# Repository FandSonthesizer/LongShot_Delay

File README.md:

# LongShot_Delay
This is the evolution of our wire-head delay pedal. Here we add a wobble effect top simulate a worn tape drive, where the motors and belts are quite old.

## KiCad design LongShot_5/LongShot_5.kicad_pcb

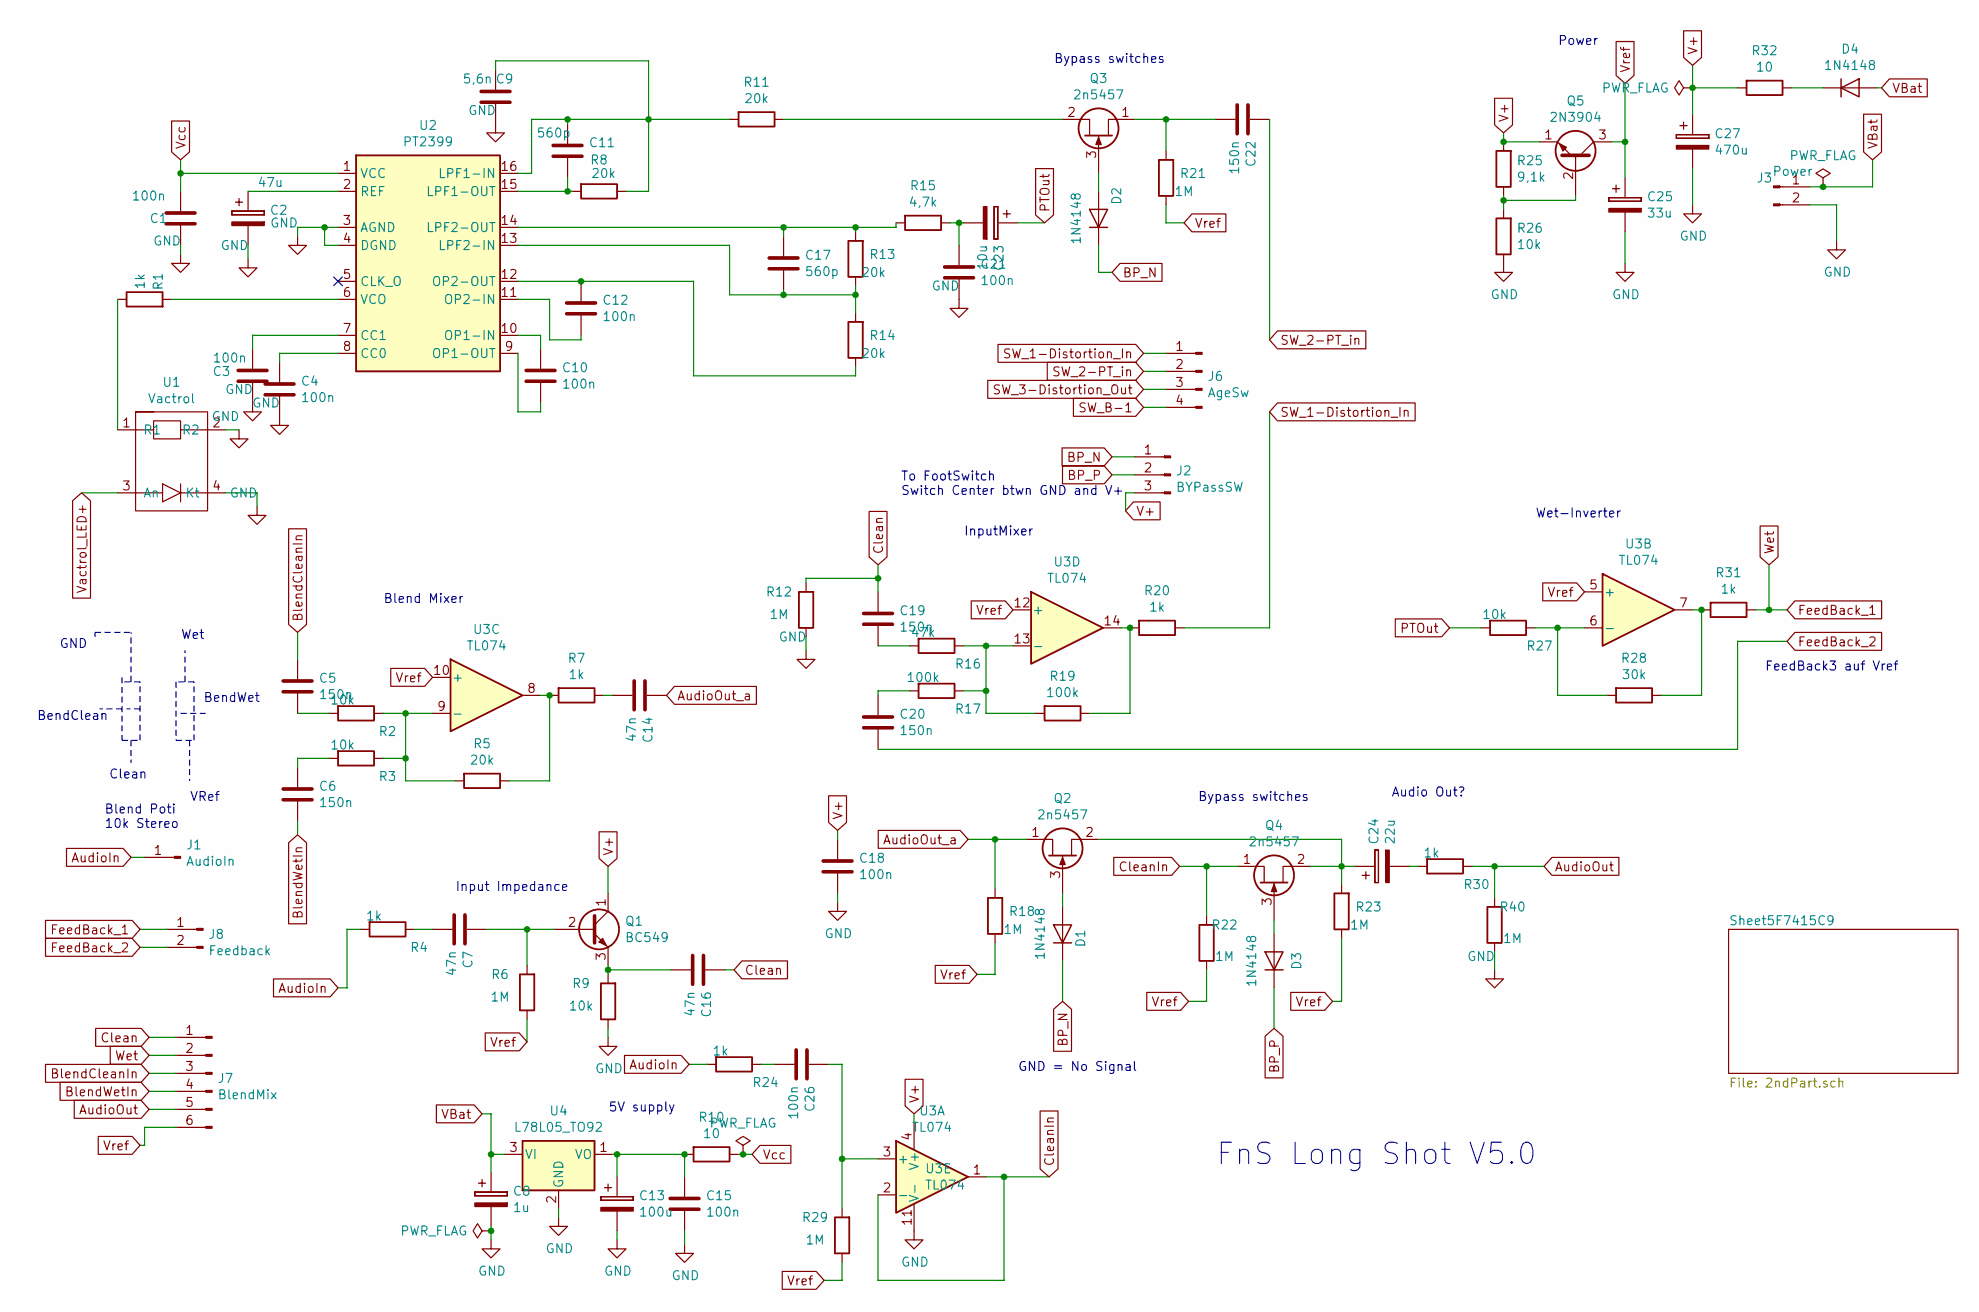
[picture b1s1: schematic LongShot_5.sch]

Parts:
C1, C3, C4, C10, C12, C15, C18, C21, C26: 100n; Kondensator_Keramik
C2: 47u; Elko_D6.3mm_P2.50mm
C5, C6, C19, C20, C22: 150n; Kondensator_Keramik
C7, C14, C16: 47n; Kondensator_Keramik
C8: 1u; Elko_D6.3mm_P2.50mm
C9: 5,6n; Kondensator_Keramik
C11, C17: 560p; Kondensator_Keramik
C13: 100u; Elko_D6.3mm_P2.50mm
C23: 10u; Elko_D6.3mm_P2.50mm
C24: 22u; Elko_D6.3mm_P2.50mm
C25: 33u; Elko_D6.3mm_P2.50mm
C27: 470u; Elko_D6.3mm_P2.50mm
D1, D2, D3, D4: 1N4148; Diode_Horizontal
J1: AudioIn; Stift
J2: BYPassSW; Stift_0x3
J3: Power; Stift_x02
J6: AgeSw; PinHeader_1x04_P2.54mm_Vertical_NIK
J7: BlendMix; PinHeader_1x06_P2.54mm_Vertical_NIK
J8: Feedback; Stift_x02
Q1: BC549; TO-92_Wide_NIK
Q2, Q3, Q4: 2n5457; TO-92_Wide_NIK
Q5: 2N3904; TO-92_Wide_NIK
R1, R4, R7, R20, R24, R30, R31: 1k; Widerstand_liegend
R2, R3, R9, R26, R27: 10k; Widerstand_liegend
R5, R8, R11, R13, R14: 20k; Widerstand_liegend
R6, R12, R18, R21, R22, R23, R29, R40: 1M; Widerstand_liegend
R10, R32: 10; Widerstand_liegend
R15: 4,7k; Widerstand_liegend
R16: 47k; Widerstand_liegend
R17, R19: 100k; Widerstand_liegend
R25: 9,1k; Widerstand_liegend
R28: 30k; Widerstand_liegend
U1: Vactrol
U2: PT2399; DIP-16_W7.62mm_Socket_LongPads
U3: TL074; DIP-14_W7.62mm_Socket_LongPads
U4: L78L05_TO92; TO-92_Wide_NIK

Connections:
AudioIn: J1.1, R4.2, R24.2
AudioOut: J7.5, R30.1, R40.2
AudioOut_a: C14.1, Q2.1 (D), R18.2
BP_N: D1.1 (K), D2.1 (K), J2.1
BP_P: D3.1 (K), J2.2
BlendCleanIn: C5.1, J7.3
BlendWetIn: C6.2, J7.4
Clean: C16.1, C19.1, J7.1, R12.2
CleanIn: Q4.1 (D), R22.2, U3.1, U3.2 (-)
DistB_2: J6.3; also elsewhere on the board
FeedBack_1: J7.2, J8.1, R31.1
FeedBack_2: C20.2, J8.2
GND: C1.2, C2.2, C3.1, C4.1, C8.2, C9.1, C13.2, C15.2, C18.2, C21.2, C25.2, C27.2, J3.2, R9.1, R12.1, R26.1, R40.1, U1.2 (R2), U1.4 (Kt), U2.3 (AGND), U2.4 (DGND), U3.11 (V-), U4.2 (GND); also elsewhere on the board
unnamed: C2.1, U2.2 (REF)
unnamed: C3.2, U2.7 (CC1)
unnamed: C4.2, U2.8 (CC0)
unnamed: C5.2, R2.2
unnamed: C6.1, R3.2
unnamed: C7.1, Q1.2 (B), R6.2
unnamed: C7.2, R4.1
unnamed: C10.1, U2.9 (OP1-OUT)
unnamed: C10.2, U2.10 (OP1-IN)
unnamed: C11.1, R8.2, U2.15 (LPF1-OUT)
unnamed: C9.2, C11.2, R8.1, R11.2, U2.16 (LPF1-IN)
unnamed: C12.1, U2.11 (OP2-IN)
unnamed: C12.2, R14.1, U2.12 (OP2-OUT)
unnamed: C13.1, C15.1, R10.2, U4.1 (VO)
unnamed: C14.2, R7.1
unnamed: C16.2, Q1.3 (E), R9.2
unnamed: C17.1, R13.2, R15.2, U2.14 (LPF2-OUT)
unnamed: C17.2, R13.1, R14.2, U2.13 (LPF2-IN)
unnamed: C19.2, R16.2
unnamed: C20.1, R17.2
unnamed: C21.1, C23.2, R15.1
unnamed: C22.2, Q3.1 (D), R21.2
unnamed: C24.1, Q2.2 (S), Q4.2 (S), R23.2
unnamed: C24.2, R30.2
unnamed: C26.1, R29.2, U3.3 (+)
unnamed: C26.2, R24.1
unnamed: D1.2 (A), Q2.3 (G)
unnamed: D2.2 (A), Q3.3 (G)
unnamed: D3.2 (A), Q4.3 (G)
unnamed: D4.1 (K), R32.1
unnamed: Q3.2 (S), R11.1
unnamed: Q5.2 (B), R25.1, R26.2
unnamed: R1.1, U1.1 (R1)
unnamed: R1.2, U2.6 (VCO)
unnamed: R2.1, R3.1, R5.2, U3.9 (-)
unnamed: R5.1, R7.2, U3.8
unnamed: R16.1, R17.1, R19.2, U3.13 (-)
unnamed: R19.1, R20.2, U3.14
unnamed: R27.1, R28.2, U3.6 (-)
unnamed: R28.1, R31.2, U3.7
PTOut: C23.1, R27.2
SW_1-Distortion_In: J6.1, R20.1; also elsewhere on the board
SW_2-PT_in: C22.1, J6.2
SW_B-1: J6.4; also elsewhere on the board
V+: C18.1, C27.1, J2.3, Q1.1 (C), Q5.1 (E), R25.2, R32.2, U3.4 (V+); also elsewhere on the board
VBat: C8.1, D4.2 (A), J3.1, U4.3 (VI)
Vactrol_LED+: U1.3 (An); also elsewhere on the board
Vcc: C1.1, R10.1, U2.1 (VCC)
Vref: C25.1, J7.6, Q5.3 (C), R6.1, R18.1, R21.1, R22.1, R23.1, R29.1, U3.5 (+), U3.10 (+), U3.12 (+); also elsewhere on the board

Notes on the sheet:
FnS Long Shot V5.0
Wet
Clean
BendClean
BendWet
Blend Poti 10k Stereo
Blend Mixer
Power
5V supply
VRef
GND
InputMixer
Wet-Inverter
Input Impedance
FeedBack3 auf Vref
Bypass switches
GND = No Signal
To FootSwitch Switch Center btwn GND and V+
Audio Out?

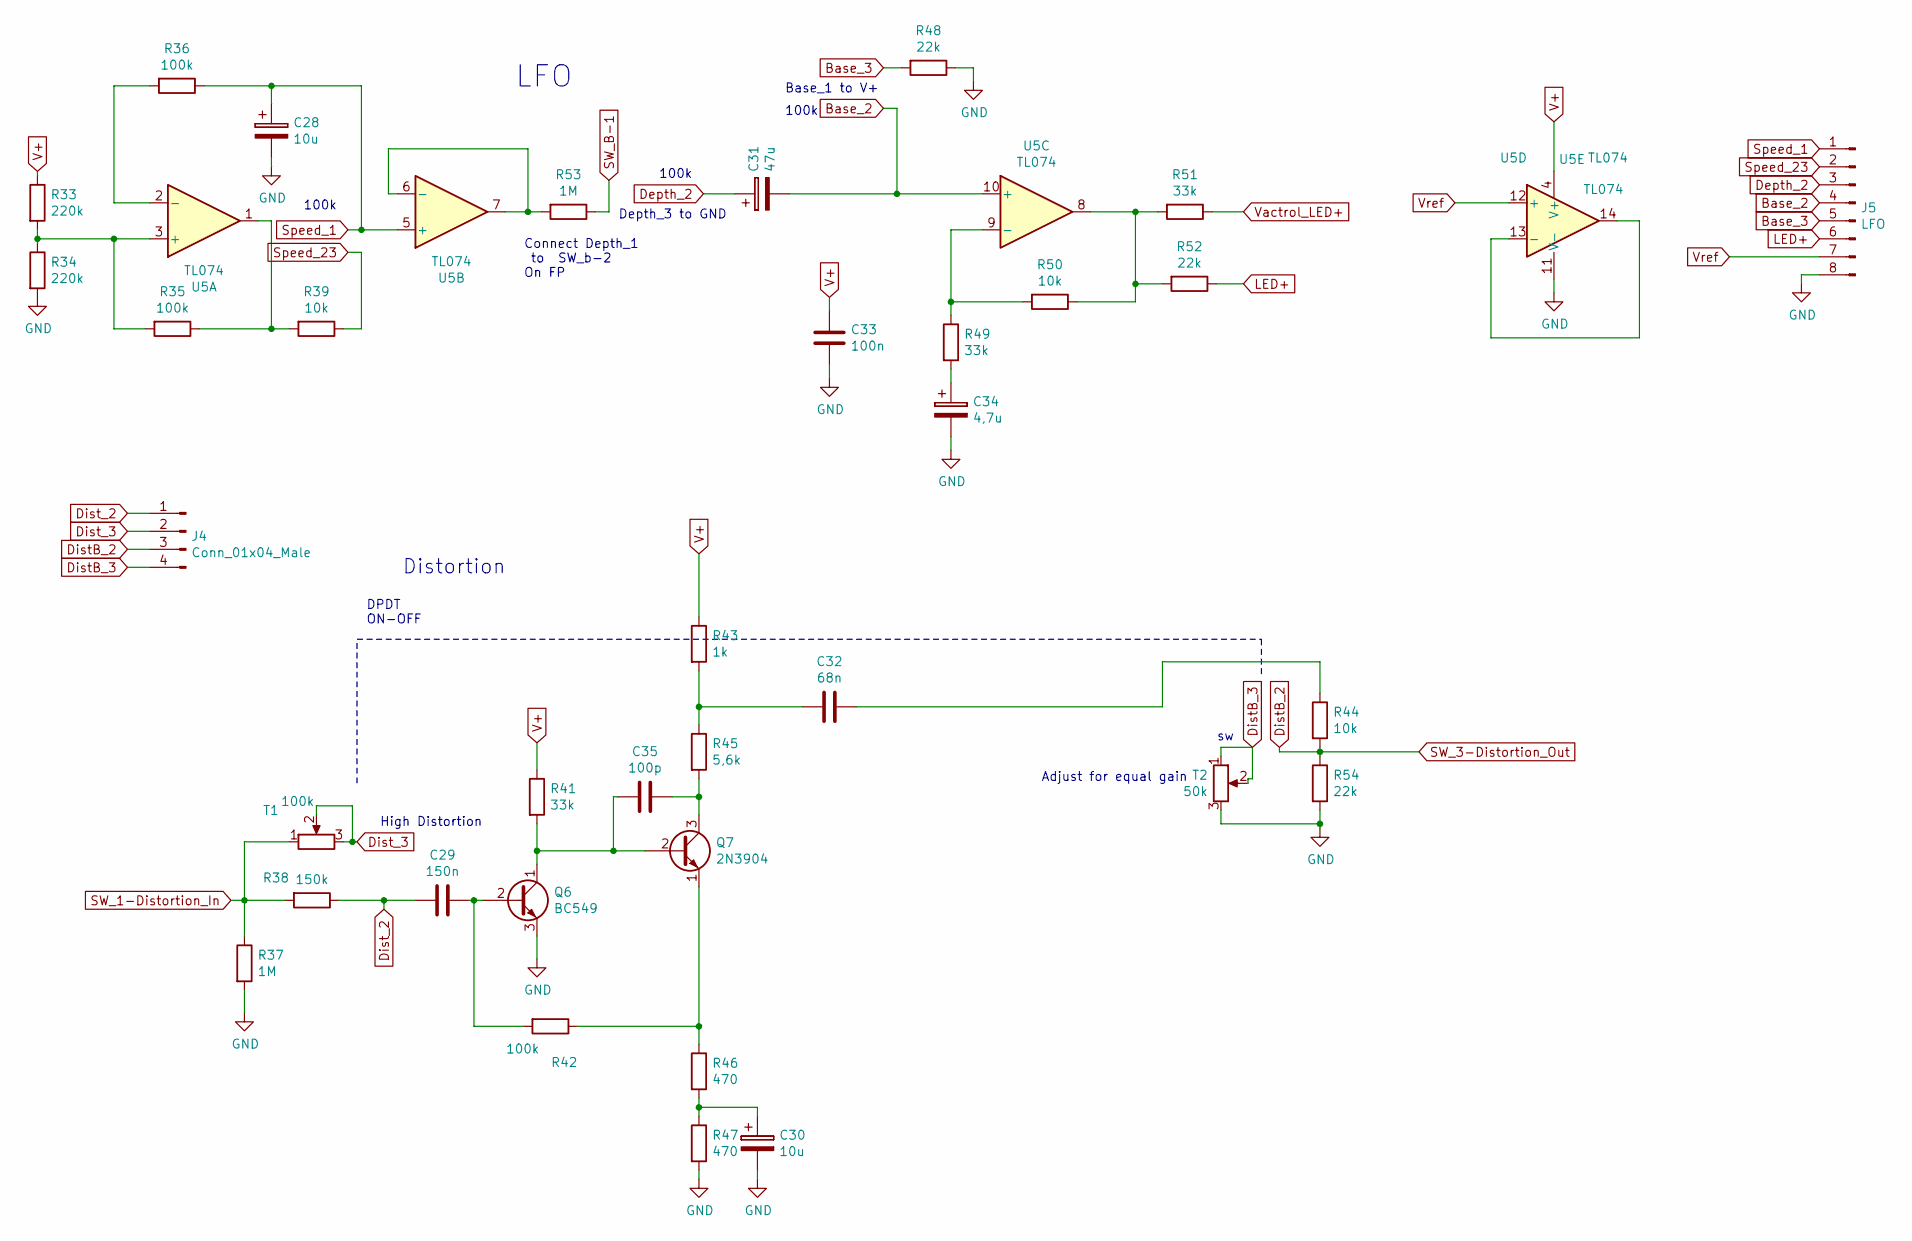
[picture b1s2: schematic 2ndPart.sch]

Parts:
C28, C30: 10u; Elko_D6.3mm_P2.50mm
C29: 150n; Kondensator_Keramik
C31: 47u; Elko_D6.3mm_P2.50mm
C32: 68n; Kondensator_Keramik
C33: 100n; Kondensator_Keramik
C34: 4,7u; Elko_D6.3mm_P2.50mm
C35: 100p; Kondensator_Keramik
J4: Conn_01x04_Male; PinHeader_1x04_P2.54mm_Vertical_NIK
J5: LFO; PinHeader_1x08_P2.54mm_Vertical_Nik
Q6: BC549; TO-92_Wide_NIK
Q7: 2N3904; TO-92_Wide_NIK
R33, R34: 220k; Widerstand_liegend
R35, R36, R42: 100k; Widerstand_liegend
R37, R53: 1M; Widerstand_liegend
R38: 150k; Widerstand_liegend
R39, R44, R50: 10k; Widerstand_liegend
R41, R49, R51: 33k; Widerstand_liegend
R43: 1k; Widerstand_liegend
R45: 5,6k; Widerstand_liegend
R46, R47: 470; Widerstand_liegend
R48, R52, R54: 22k; Widerstand_liegend
T1: 100k; Trimmer_Vertical
T2: 50k; Trimmer_Vertical
U5: TL074; DIP-14_W7.62mm_Socket_LongPads

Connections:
Base_2: C31.2, J5.4, U5.10 (+)
Base_3: J5.5, R48.2
Depth_2: C31.1, J5.3
DistB_2: J4.3, R44.2, R54.1; also elsewhere on the board
DistB_3: J4.4, T2.1, T2.2
Dist_2: C29.2, J4.1, R38.1
Dist_3: J4.2, T1.2, T1.3
GND: C28.2, C30.2, C33.1, C34.2, J5.8, Q6.3 (E), R34.2, R37.2, R47.2, R48.1, R54.2, T2.3, U5.11 (V-); also elsewhere on the board
LED+: J5.6, R52.1
unnamed: C29.1, Q6.2 (B), R42.2
unnamed: C30.1, R46.2, R47.1
unnamed: C32.1, R44.1
unnamed: C32.2, R43.2, R45.1
unnamed: C34.1, R49.2
unnamed: C35.1, Q7.3 (C), R45.2
unnamed: C35.2, Q6.1 (C), Q7.2 (B), R41.2
unnamed: Q7.1 (E), R42.1, R46.1
unnamed: R33.2, R34.1, R35.2, U5.3 (+)
unnamed: R35.1, R39.2, U5.1
unnamed: R36.2, U5.2 (-)
unnamed: R49.1, R50.2, U5.9 (-)
unnamed: R50.1, R51.2, R52.2, U5.8
unnamed: R53.2, U5.6 (-), U5.7
unnamed: U5.13 (-), U5.14
SW_1-Distortion_In: R37.1, R38.2, T1.1; also elsewhere on the board
SW_B-1: R53.1; also elsewhere on the board
Speed_1: C28.1, J5.1, R36.1, U5.5 (+)
Speed_23: J5.2, R39.1
V+: C33.2, R33.1, R41.1, R43.1, U5.4 (V+); also elsewhere on the board
Vactrol_LED+: R51.1; also elsewhere on the board
Vref: J5.7, U5.12 (+); also elsewhere on the board

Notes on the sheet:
DPDT ON-OFF
Distortion
100k
High Distortion
Base_1 to V+
Depth_3 to GND
Connect Depth_1 to SW_b-2 On FP
LFO
Adjust for equal gain

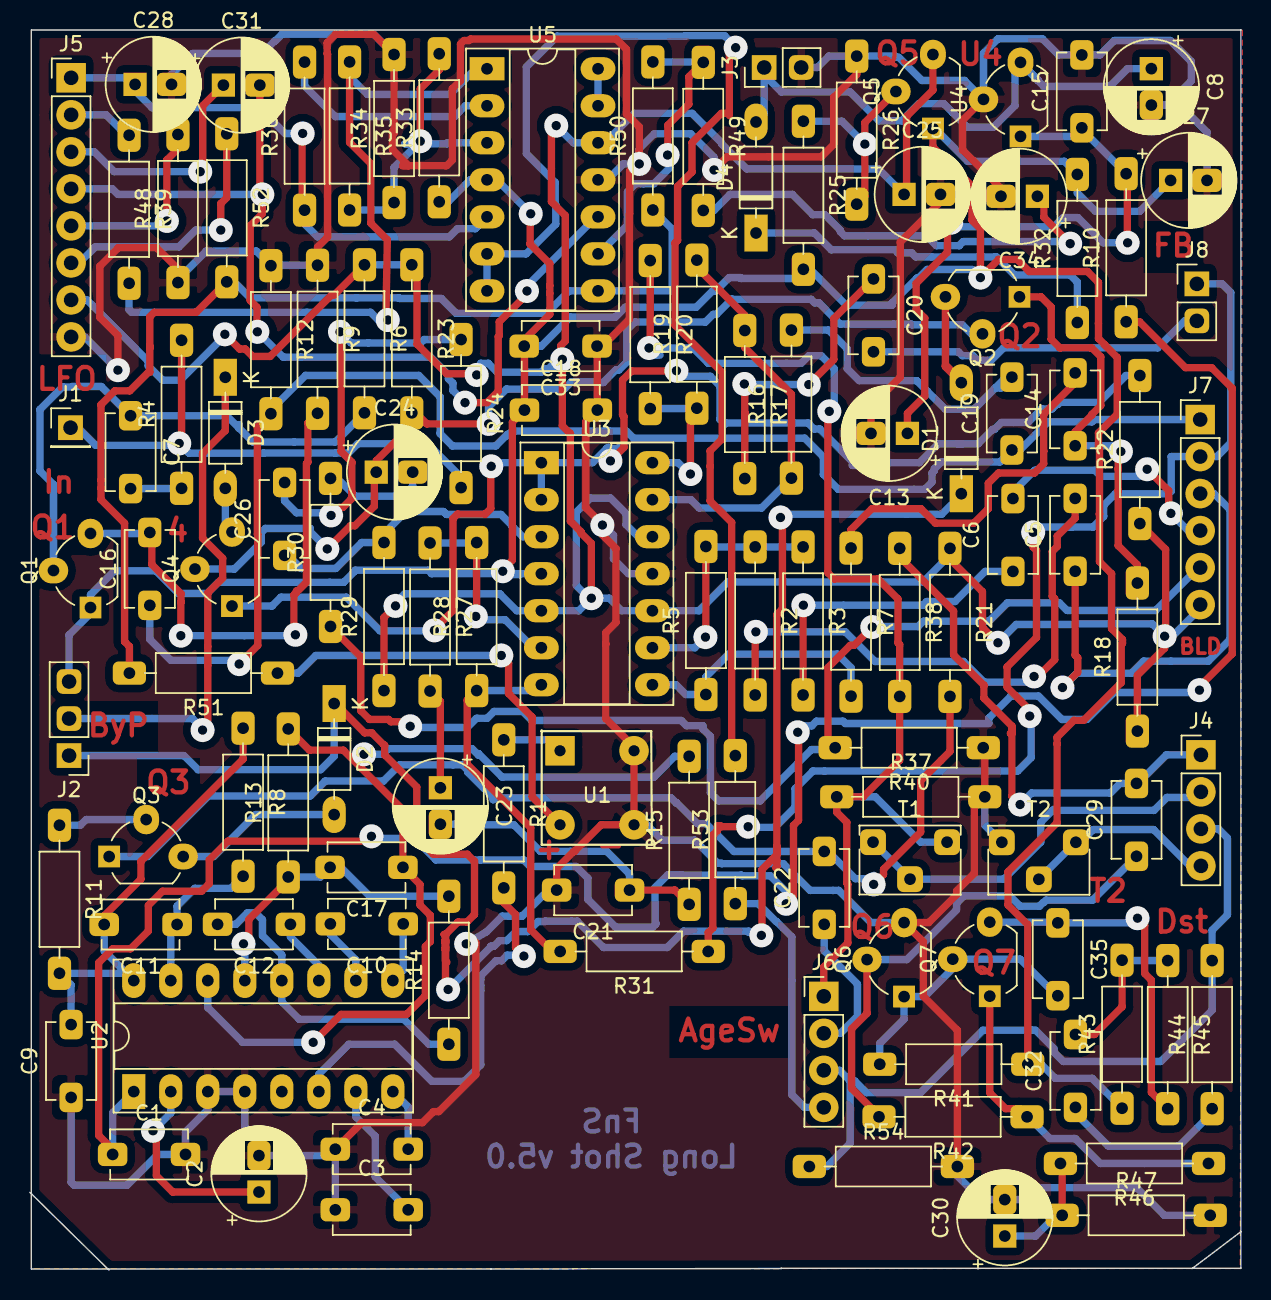
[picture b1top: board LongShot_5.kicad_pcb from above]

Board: 2 copper layers, 83.1 x 85.1 mm, 115 parts (0 on the bottom side), 86 nets.
